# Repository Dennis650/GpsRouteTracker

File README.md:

# GpsRouteTracker

## Build status

## Important

!!!EXPERIMENTAL SOFTWARE!!!

!!!EXPERIMENTAL ELECTRICAL CIRCUIT!!!

!!!USE AT YOUR OWN RISK!!!

!!!Do not use the software / circuit / device while driving!!!

## Features

- saves tracks as GPX Files to SD-Card
- saves waypoints to SD-CARD
- Display: 
    -  Compass
    - Fuelmaster
    - Tripmaster
    - Lap StopWatch
    - temperature
    - Direction and distance to a destination or home
- WebInterface (WIFI)
    - download and delete your tracks via 
- Bluetooth / BLE
    - display gps-data
    - edit destination and home location with your smartphone (Bluetooth/BLE)

## Videos

*GpsRouteTracker in action*

*Bluetooth (BLE) - Gps-data and edit destination and home location with your smartphone*

## Circuit

## Parts
- WEMOS LOLIN32 V1.0.0
- 1.5" 128x128 OLED Display solid white
- ublox NEO-6M seriell GPS-Module
- micro sd breakout board 3,3V 6Pin
- SD-Card
- LM1117-3.3
- OKI-78SR-5_1.5-W36-C
- 4 x 10 kOhm
- 1 x 4.7 kOhm
- 3 x 12mm push buttons
- DS18B20 waterproof

## Build and flash to ESP32

connect your ESP32 with USB to your Computer.

You can edit or ad you own bike to platformio/include/bikes. Copy a existing bike and modify the settings. Add your bike also to platformio/platformio.ini

```platformio run -e Prototype --target upload```

## Cases / 3D-Print

https://www.thingiverse.com/thing:6894891

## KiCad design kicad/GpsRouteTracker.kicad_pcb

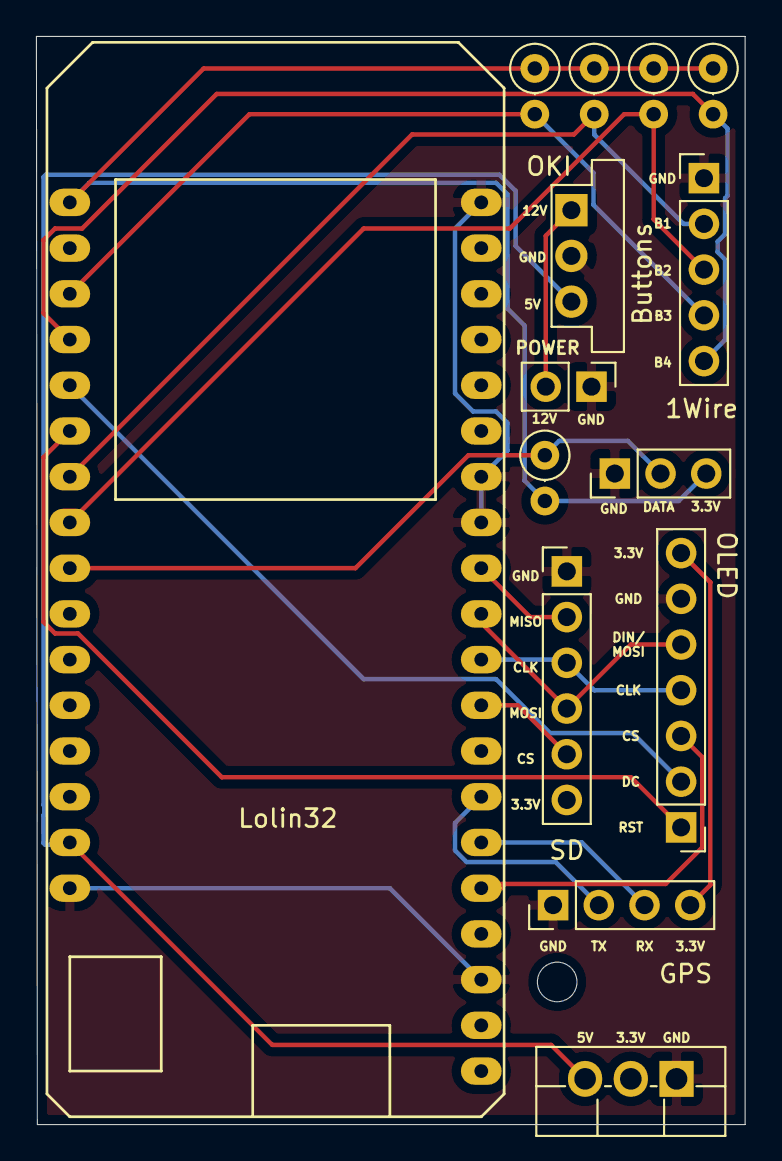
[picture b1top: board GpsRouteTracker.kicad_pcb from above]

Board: 2 copper layers, 39.4 x 60.5 mm, 14 parts (0 on the bottom side), 19 nets.

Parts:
J1: Power; PinHeader_1x02_P2.54mm_Vertical
J2: OneWire; PinHeader_1x03_P2.54mm_Vertical
J3: GPS; PinHeader_1x04_P2.54mm_Vertical
J4: SD; PinHeader_1x06_P2.54mm_Vertical
J5: OLED; PinHeader_1x07_P2.54mm_Vertical
J6: Buttons; PinHeader_1x05_P2.54mm_Vertical
OKI: OKI-78SR-5_1.5-W36-C; Converter_DCDC_muRata_OKI-78SR_Vertical
R1, R2, R3, R4, R5: R; R_Axial_DIN0207_L6.3mm_D2.5mm_P2.54mm_Vertical
U1: Lolin32
U2: LM1117-3.3; TO-220F-3_Vertical

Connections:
+3V3: J3.4, J4.6, J5.7, U2.2
+5V: OKI.3, U1.15, U2.3
+12V: J1.2, OKI.1
/3.3V: J2.3, R1.1, R2.1, R3.1, R4.2, R5.1, U1.1
/B1: J6.2, R1.2, U1.7
/B2: J6.3, R2.2, U1.8
/B3: J6.4, R3.2, U1.3
/B4: J6.5, R5.2, U1.4
/CLK: J4.3, J5.4, U1.27
/MISO: J4.2, U1.25
/MOSI: J4.4, J5.5, U1.26
/OLED-CS: J5.3, U1.32
/OLED-DC: J5.2, U1.5
/OLED-RST: J5.1, U1.6
/RX: J3.3, U1.31
/SD-CS: J4.5, U1.28
/TX: J3.2, U1.30
GND: J1.1, J2.1, J3.1, J4.1, J5.6, J6.1, OKI.2, U1.16, U1.17, U1.23, U1.24, U1.34, U2.1
unnamed: J2.2, R4.1, U1.9

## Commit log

2023-04-14 Bump SdFat to 2.2.2
2023-04-30 Bump espressif32 to 6.2.0
2023-05-20 Bump espressif32 to 6.3.0
2023-05-22 Bump U8g2 to 2.34.18
2023-05-27 Bump espressif32 to 6.3.1
2023-06-15 Bump U8g2 to 2.34.20
2023-06-19 Bump U8g2 to 2.34.22
2023-06-21 Bump espressif32 to 6.3.2
2023-06-24 expressif 6.3.2 und u8g 2.34.22
2023-07-04 Bump U8g2 to 2.35.2
2023-07-16 Bump U8g2 to 2.35.3
2023-07-24 Bump U8g2 to 2.35.4
2023-09-12 Bump U8g2 to 2.35.6
2023-09-12 Bump espressif32 to 6.4.0
2023-09-25 Bump U8g2 to 2.35.7
2023-09-27 New Version
2023-12-03 Bump U8g2 to 2.35.8
2023-12-12 Bump OneWire to 2.3.8
2023-12-27 Bump U8g2 to 2.35.9
2023-12-28 Bump espressif32 to 6.5.0
2024-10-11 Switch to https to call GpsRoutes Endpoint
2024-10-11 Update dependencies
2024-10-11 Show Messages when interacting with GpsRoutes
2024-12-31 Link to Thingiverse
